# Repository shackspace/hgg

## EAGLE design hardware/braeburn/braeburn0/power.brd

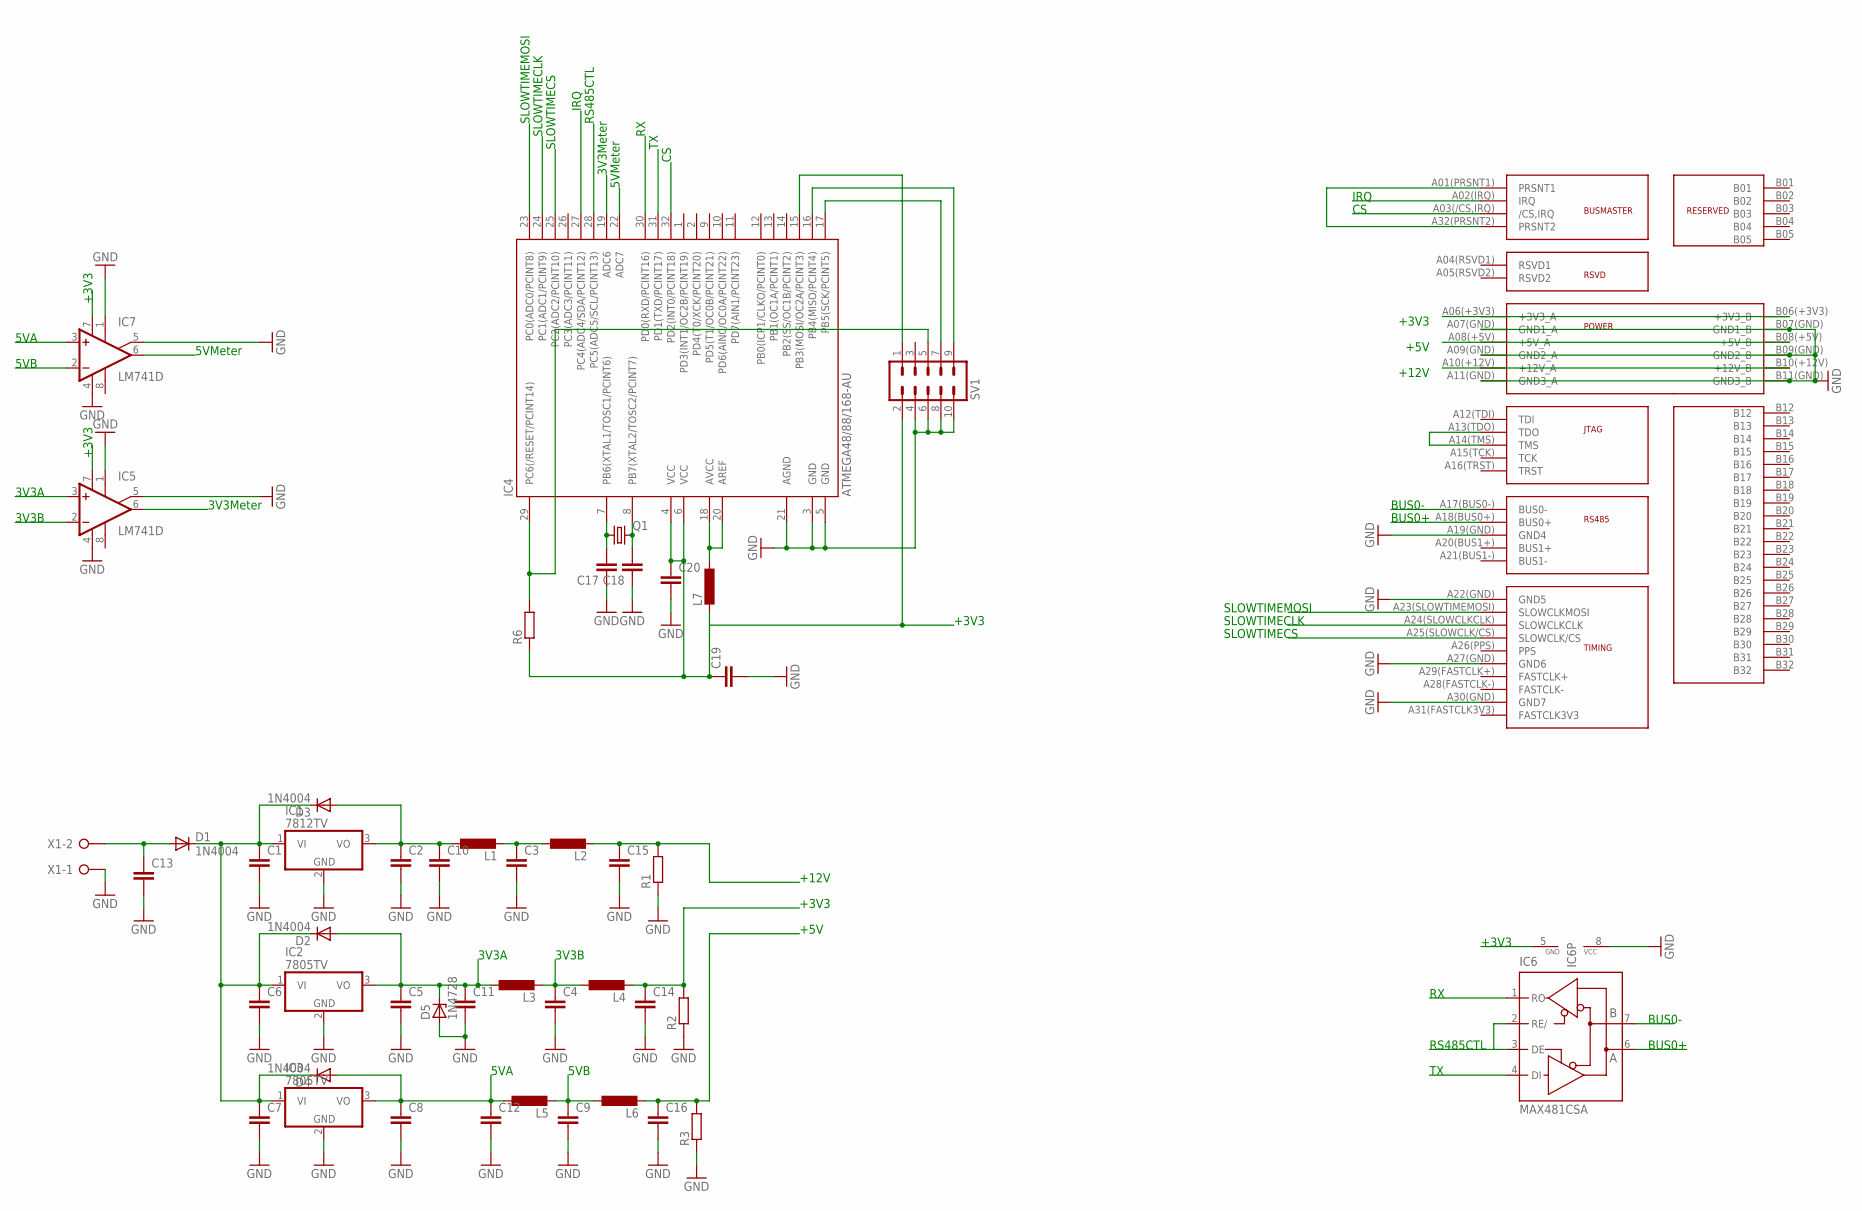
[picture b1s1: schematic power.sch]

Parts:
C1, C2, C3, C4, C5, C6, C7, C8, C9, C17, C18, C19, C20: C-EUC0805; C0805
C10, C11, C12: C-EU025-050X050; C025-050X050
C13: C-EU025-060X050; C025-060X050
C14, C15, C16: C2.5/6; C2.5-6
D1, D2, D3, D4: 1N4004; DO41-10
D5: 1N4728; DO41Z10
IC1: 7812TV; TO220V
IC2, IC3: 7805TV; TO220V
IC4: ATMEGA48/88/168-AU; TQFP32-08
IC5, IC7: LM741D; SO08
IC6: MAX481CSA; SO08
L1, L2, L3, L4, L5, L6, L7: L-EU0207/5V; 0207/5V
Q1: CRYSTALHC49U-V; HC49U-V
R1, R2, R3: R-EU_0207/15; 0207/15
R6: R-EU_R0805; R0805
SV1: MA05-2
U$1: FRIENDSHIPCONNECTOR; FRIENDSHIP_EDGE_CONNECTOR
U$2: HGG_LOGO
X1: W237-02P; W237-132

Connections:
3V3A: C5.1, C11.1, D2.A, D5.C, IC2.3 (VO), IC5.3 (+IN), L3.1
3V3B: C4.1, IC5.2 (-IN), L3.2, L4.1
3V3METER: IC4.19 (ADC6), IC5.6 (OUT)
5VA: C8.1, C12.1, D4.A, IC3.3 (VO), IC7.3 (+IN), L5.1
5VB: C9.1, IC7.2 (-IN), L5.2, L6.1
5VMETER: IC4.22 (ADC7), IC7.6 (OUT)
+3V3: C14.1, C19.1, C20.1, IC4.4 (VCC), IC4.6 (VCC), IC5.7 (V+), IC6.5 (GND), IC7.7 (V+), L4.2, L7.2, R2.2, R6.1, SV1.2, U$1.A06(+3V3) (+3V3_A), U$1.B06(+3V3) (+3V3_B)
+5V: C16.1, L6.2, R3.2, U$1.A08(+5V) (+5V_A), U$1.B08(+5V) (+5V_B)
+12V: C15.1, L2.2, R1.2, U$1.A10(+12V) (+12V_A), U$1.B10(+12V) (+12V_B)
BUS0+: IC6.6 (A), U$1.A18(BUS0+) (BUS0+)
BUS0-: IC6.7 (B), U$1.A17(BUS0-) (BUS0-)
BUSCTL: IC4.28 (PC5(ADC5/SCL/PCINT13)), IC6.2 (RE/), IC6.3 (DE)
CS: IC4.32 (PD2(INT0/PCINT18)), U$1.A03(/CS,IRQ) (/CS,IRQ)
GND: C1.2, C2.2, C3.2, C4.2, C5.2, C6.2, C7.2, C8.2, C9.2, C10.2, C11.2, C12.2, C13.2, C14.2, C15.2, C16.2, C17.1, C18.1, C19.2, C20.2, D5.A, IC1.2 (GND), IC2.2 (GND), IC3.2 (GND), IC4.3 (GND), IC4.5 (GND), IC4.21 (AGND), IC5.1 (ON1), IC5.4 (V-), IC5.5 (ON2), IC6.8 (VCC), IC7.1 (ON1), IC7.4 (V-), IC7.5 (ON2), R1.1, R2.1, R3.1, SV1.4, SV1.6, SV1.8, SV1.10, U$1.A07(GND) (GND1_A), U$1.A09(GND) (GND2_A), U$1.A11(GND) (GND3_A), U$1.A19(GND) (GND4), U$1.A22(GND) (GND5), U$1.A27(GND) (GND6), U$1.A30(GND) (GND7), U$1.B07(GND) (GND1_B), U$1.B09(GND) (GND2_B), U$1.B11(GND) (GND3_B), X1.1
IRQ: IC4.27 (PC4(ADC4/SDA/PCINT12)), U$1.A02(IRQ) (IRQ)
unnamed: C1.1, C6.1, C7.1, D1.C, D2.C, D3.C, D4.C, IC1.1 (VI), IC2.1 (VI), IC3.1 (VI)
unnamed: C18.2, IC4.8 (PB7(XTAL2/TOSC2/PCINT7)), Q1.2
unnamed: C2.1, C10.1, D3.A, IC1.3 (VO), L1.1
unnamed: C3.1, L1.2, L2.1
unnamed: C13.1, D1.A, X1.2
unnamed: C17.2, IC4.7 (PB6(XTAL1/TOSC1/PCINT6)), Q1.1
unnamed: IC4.29 (PC6(/RESET/PCINT14)), R6.2, SV1.5
unnamed: IC4.18 (AVCC), IC4.20 (AREF), L7.1
unnamed: IC4.16 (PB4(MISO/PCINT4)), SV1.9
unnamed: IC4.17 (PB5(SCK/PCINT5)), SV1.7
unnamed: IC4.15 (PB3(MOSI/OC2A/PCINT3)), SV1.1
unnamed: U$1.A13(TDO) (TDO), U$1.A14(TMS) (TMS)
unnamed: U$1.A01(PRSNT1) (PRSNT1), U$1.A32(PRSNT2) (PRSNT2)
RX: IC4.30 (PD0(RXD/PCINT16)), IC6.1 (RO)
SLOWTIMECLK: IC4.24 (PC1(ADC1/PCINT9)), U$1.A24(SLOWCLKCLK) (SLOWCLKCLK)
SLOWTIMECS: IC4.25 (PC2(ADC2/PCINT10)), U$1.A25(SLOWCLK/CS) (SLOWCLK/CS)
SLOWTIMEMOSI: IC4.23 (PC0(ADC0/PCINT8)), U$1.A23(SLOWTIMEMOSI) (SLOWCLKMOSI)
TX: IC4.31 (PD1(TXD/PCINT17)), IC6.4 (DI)

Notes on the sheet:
BUS0-
BUS0+
RS485CTL
IRQ
+5V
+3V3
+12V
SLOWTIMEMOSI
SLOWTIMECLK
SLOWTIMECS
3V3Meter
5VMeter
3V3A
3V3B
5VA
5VB

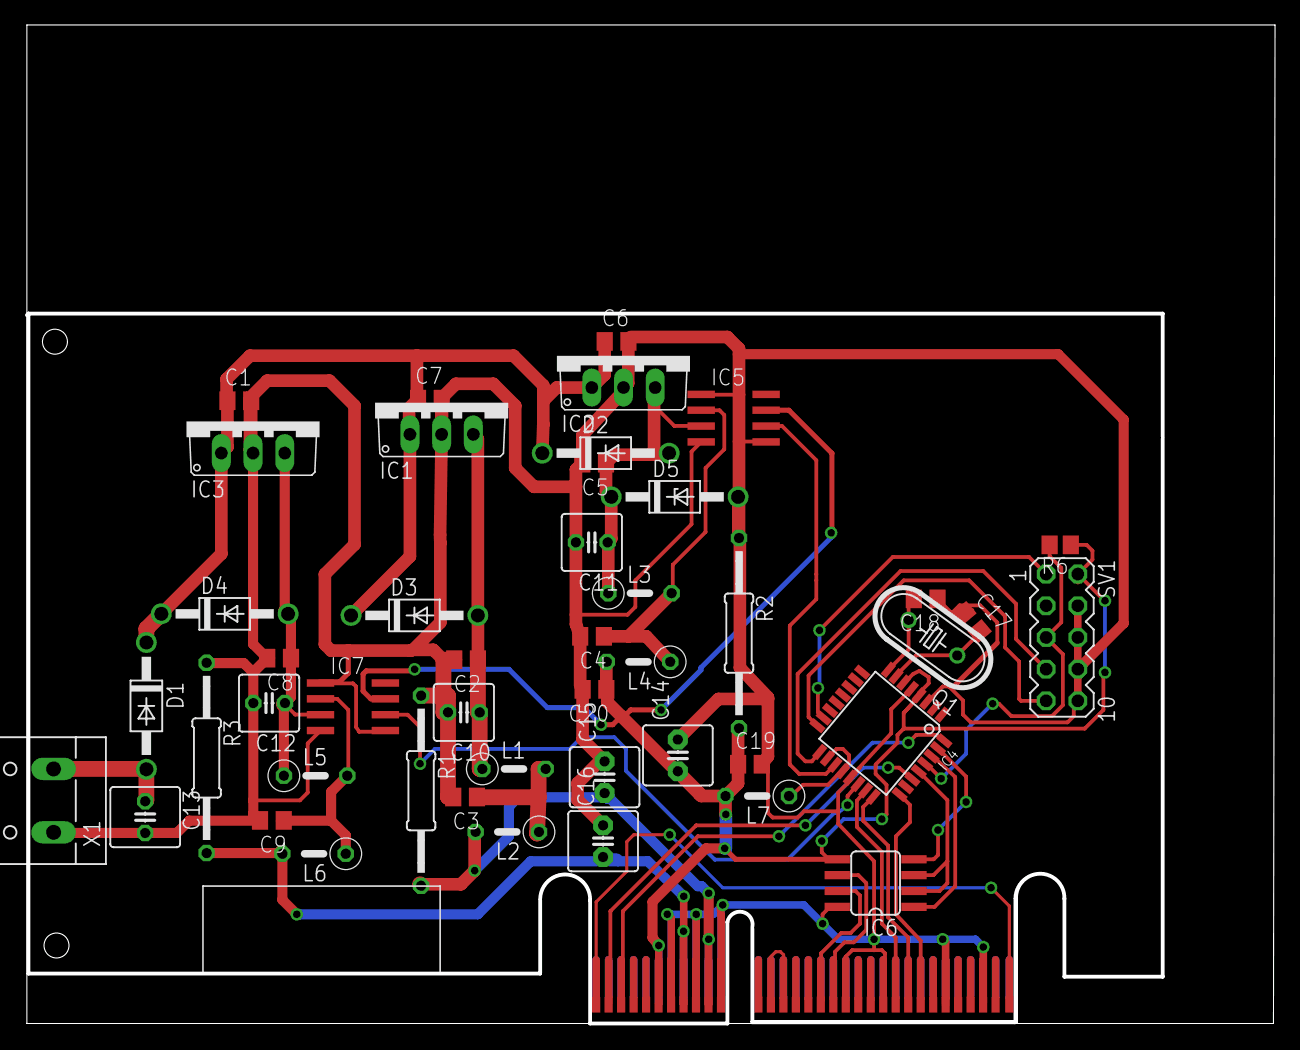
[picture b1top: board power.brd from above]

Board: 2 copper layers, 100.0 x 80.0 mm, 48 parts (0 on the bottom side), 33 nets.

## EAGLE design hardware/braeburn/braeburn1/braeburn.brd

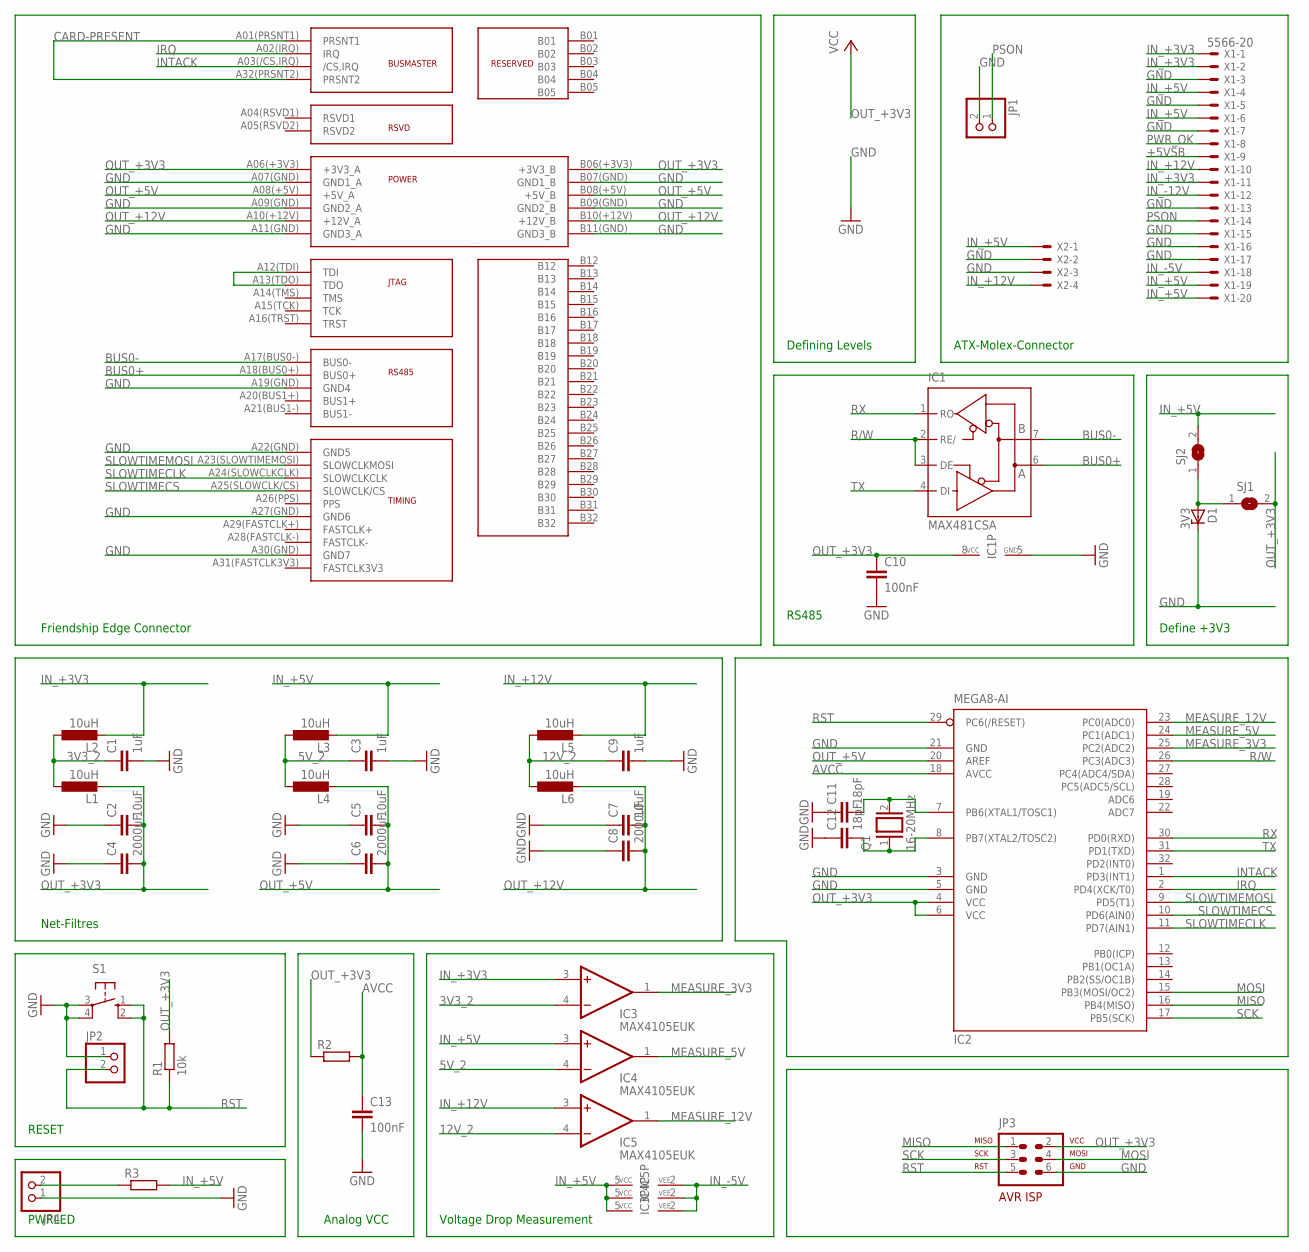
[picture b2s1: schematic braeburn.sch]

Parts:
C1, C3, C9: 1uF; C0805
C2, C5, C7: 10uF; C0603
C4, C6, C8: 2000uF; C025-060X050
C10, C13: 100nF; C0603
C11, C12: 18pF; C0603
D1: 3V3; DO41Z10
IC1: MAX481CSA; SO08
IC2: MEGA8-AI; TQFP32-08
IC3, IC4, IC5: MAX4105EUK; SOT23-5L
JP1, JP2, JP4: PINHD-1X2; 1X02
JP3: AVR-ISP-6VERT; AVR-ISP-6
L1, L2, L3, L4, L5, L6: 10uH; 0207/5V
Q1: 16-20MHz; QS
R1: 10k; R0603
R2, R3: R-EU_R0603; R0603
S1: 10-XX; B3F-10XX
SJ1, SJ2: SJW
U$1: FRIENDSHIPCONNECTOR; FRIENDSHIP_EDGE_CONNECTOR
X1: 5566-20
X2: KK-156-4

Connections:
3V3_2: C1.1, IC3.4 (-IN), L1.1, L2.1
5V_2: C3.1, IC4.4 (-IN), L3.1, L4.1
12V_2: C9.1, IC5.4 (-IN), L5.1, L6.1
+5VSB: X1.9
AVCC: C13.1, IC2.18 (AVCC), R2.2
BUS0+: IC1.6 (A), U$1.A18(BUS0+) (BUS0+)
BUS0-: IC1.7 (B), U$1.A17(BUS0-) (BUS0-)
CARD-PRESENT: U$1.A01(PRSNT1) (PRSNT1), U$1.A32(PRSNT2) (PRSNT2)
GND: C1.2, C2.1, C3.2, C4.1, C5.1, C6.1, C7.1, C8.1, C9.2, C10.2, C11.1, C12.1, C13.2, D1.C, IC1.5 (GND), IC2.3 (GND), IC2.5 (GND), IC2.21 (GND), JP1.2, JP2.1, JP3.6, JP4.1, S1.3, S1.4 (P1), U$1.A07(GND) (GND1_A), U$1.A09(GND) (GND2_A), U$1.A11(GND) (GND3_A), U$1.A19(GND) (GND4), U$1.A22(GND) (GND5), U$1.A27(GND) (GND6), U$1.A30(GND) (GND7), U$1.B07(GND) (GND1_B), U$1.B09(GND) (GND2_B), U$1.B11(GND) (GND3_B), X1.3, X1.5, X1.7, X1.13, X1.15, X1.16, X1.17, X2.2, X2.3
INTACK: IC2.1 (PD3(INT1)), U$1.A03(/CS,IRQ) (/CS,IRQ)
IN_+3V3: IC3.3 (+IN), L2.2, X1.1, X1.2, X1.11
IN_+5V: IC3.5 (VCC), IC4.3 (+IN), IC4.5 (VCC), IC5.5 (VCC), L3.2, R3.2, SJ2.2, X1.4, X1.6, X1.19, X1.20, X2.1
IN_+12V: IC5.3 (+IN), L5.2, X1.10, X2.4
IN_-5V: IC3.2 (VEE), IC4.2 (VEE), IC5.2 (VEE), X1.18
IN_-12V: X1.12
IRQ: IC2.2 (PD4(XCK/T0)), U$1.A02(IRQ) (IRQ)
MEASURE_3V3: IC2.25 (PC2(ADC2)), IC3.1 (OUT)
MEASURE_5V: IC2.24 (PC1(ADC1)), IC4.1 (OUT)
MEASURE_12V: IC2.23 (PC0(ADC0)), IC5.1 (OUT)
MISO: IC2.16 (PB4(MISO)), JP3.1
MOSI: IC2.15 (PB3(MOSI/OC2)), JP3.4
unnamed: U$1.A12(TDI) (TDI), U$1.A13(TDO) (TDO)
unnamed: JP4.2, R3.1
unnamed: C11.2, IC2.7 (PB6(XTAL1/TOSC1)), Q1.2
unnamed: C12.2, IC2.8 (PB7(XTAL2/TOSC2)), Q1.1
unnamed: D1.A, SJ1.1, SJ2.1
OUT_+3V3: C2.2, C4.2, C10.1, IC1.8 (VCC), IC2.4 (VCC), IC2.6 (VCC), JP3.2, L1.2, R1.2, R2.1, SJ1.2, U$1.A06(+3V3) (+3V3_A), U$1.B06(+3V3) (+3V3_B)
OUT_+5V: C5.2, C6.2, IC2.20 (AREF), L4.2, U$1.A08(+5V) (+5V_A), U$1.B08(+5V) (+5V_B)
OUT_+12V: C7.2, C8.2, L6.2, U$1.A10(+12V) (+12V_A), U$1.B10(+12V) (+12V_B)
PSON: JP1.1, X1.14
PWR_OK: X1.8
R/W: IC1.2 (RE/), IC1.3 (DE), IC2.26 (PC3(ADC3))
RST: IC2.29 (PC6(/RESET)), JP2.2, JP3.5, R1.1, S1.1 (S), S1.2 (S1)
RX: IC1.1 (RO), IC2.30 (PD0(RXD))
SCK: IC2.17 (PB5(SCK)), JP3.3
SLOWTIMECLK: IC2.11 (PD7(AIN1)), U$1.A24(SLOWCLKCLK) (SLOWCLKCLK)
SLOWTIMECS: IC2.10 (PD6(AIN0)), U$1.A25(SLOWCLK/CS) (SLOWCLK/CS)
SLOWTIMEMOSI: IC2.9 (PD5(T1)), U$1.A23(SLOWTIMEMOSI) (SLOWCLKMOSI)
TX: IC1.4 (DI), IC2.31 (PD1(TXD))

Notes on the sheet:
ATX-Molex-Connector
Friendship Edge Connector
RS485
Net-Filtres
RESET
Analog VCC
Voltage Drop Measurement
Defining Levels
Define +3V3
PWRLED

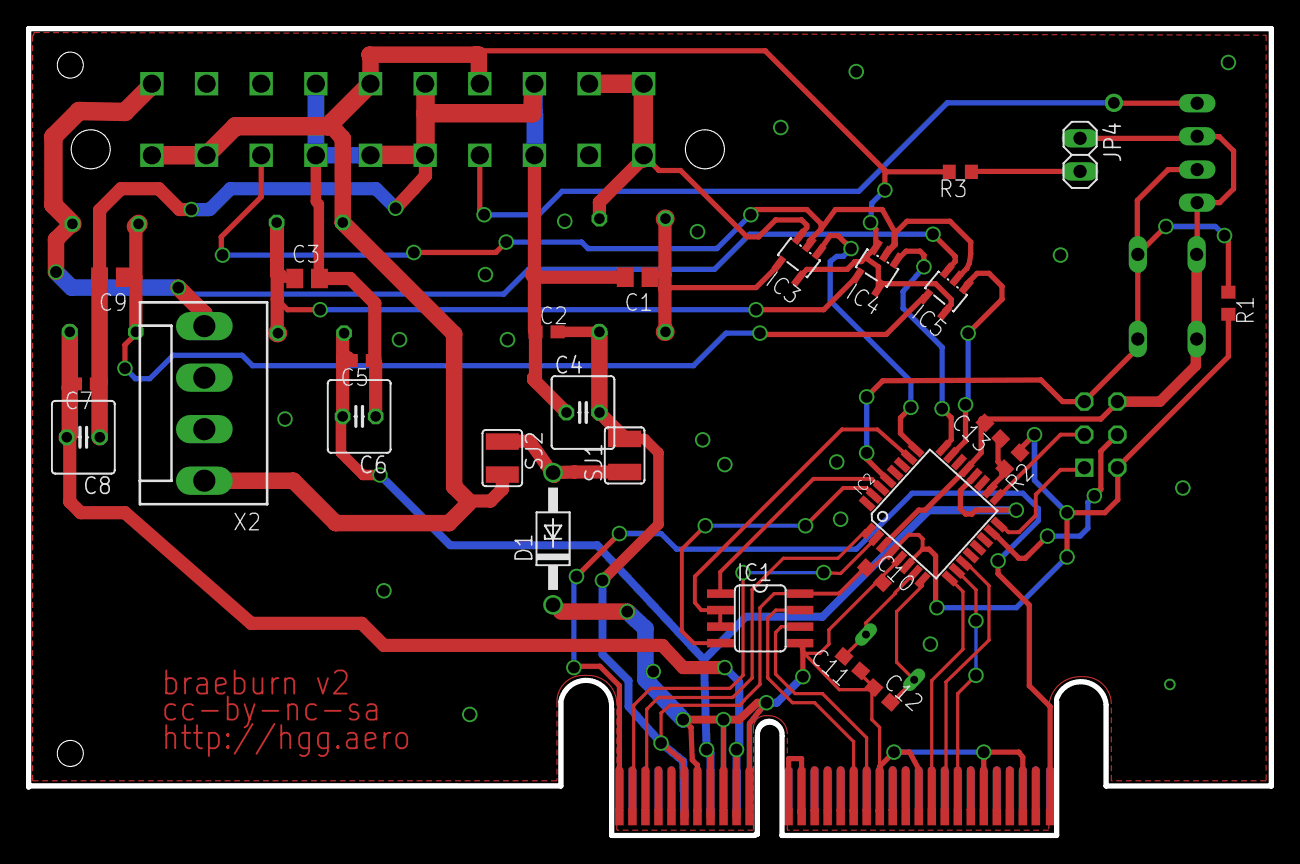
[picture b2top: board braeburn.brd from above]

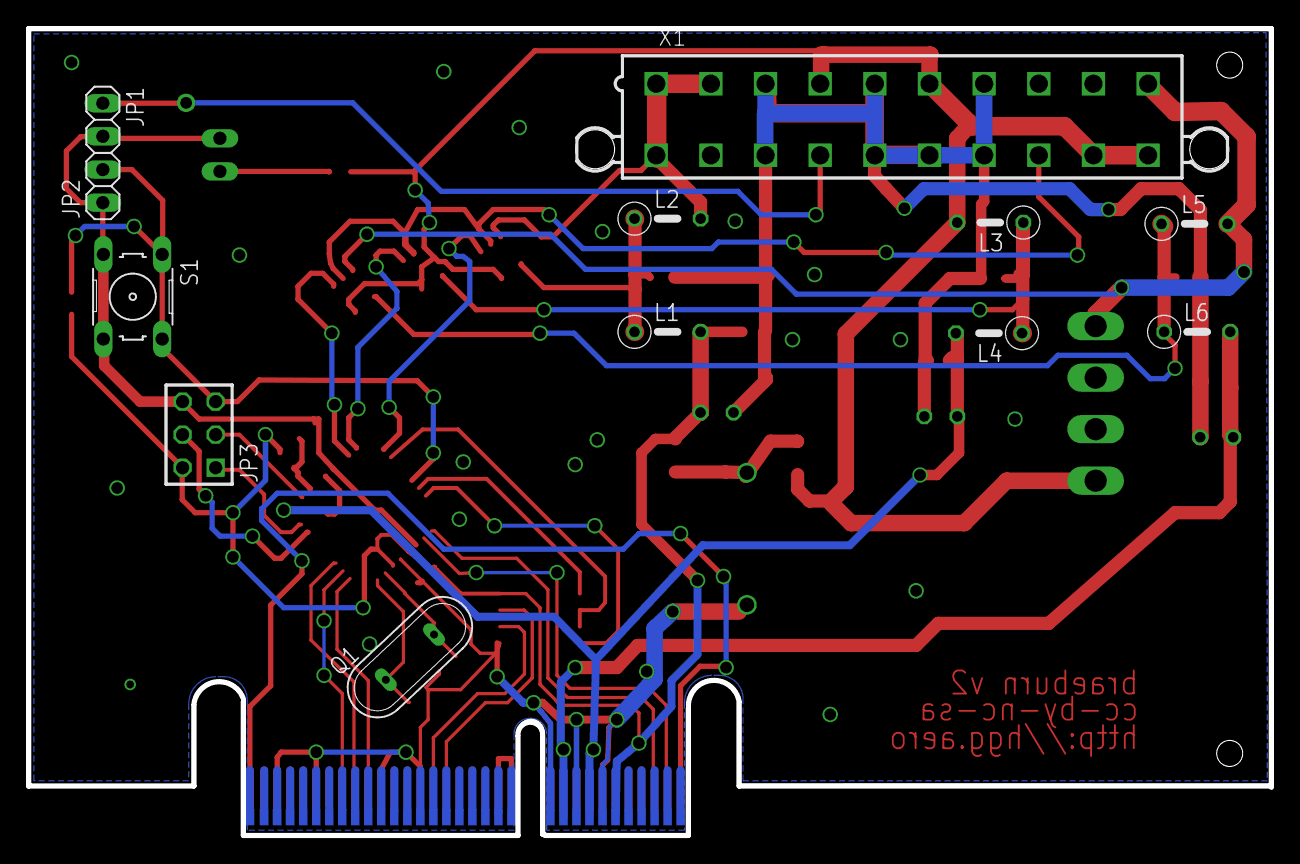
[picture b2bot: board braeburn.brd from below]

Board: 4 copper layers, 95.5 x 62.0 mm, 39 parts (12 on the bottom side), 36 nets.

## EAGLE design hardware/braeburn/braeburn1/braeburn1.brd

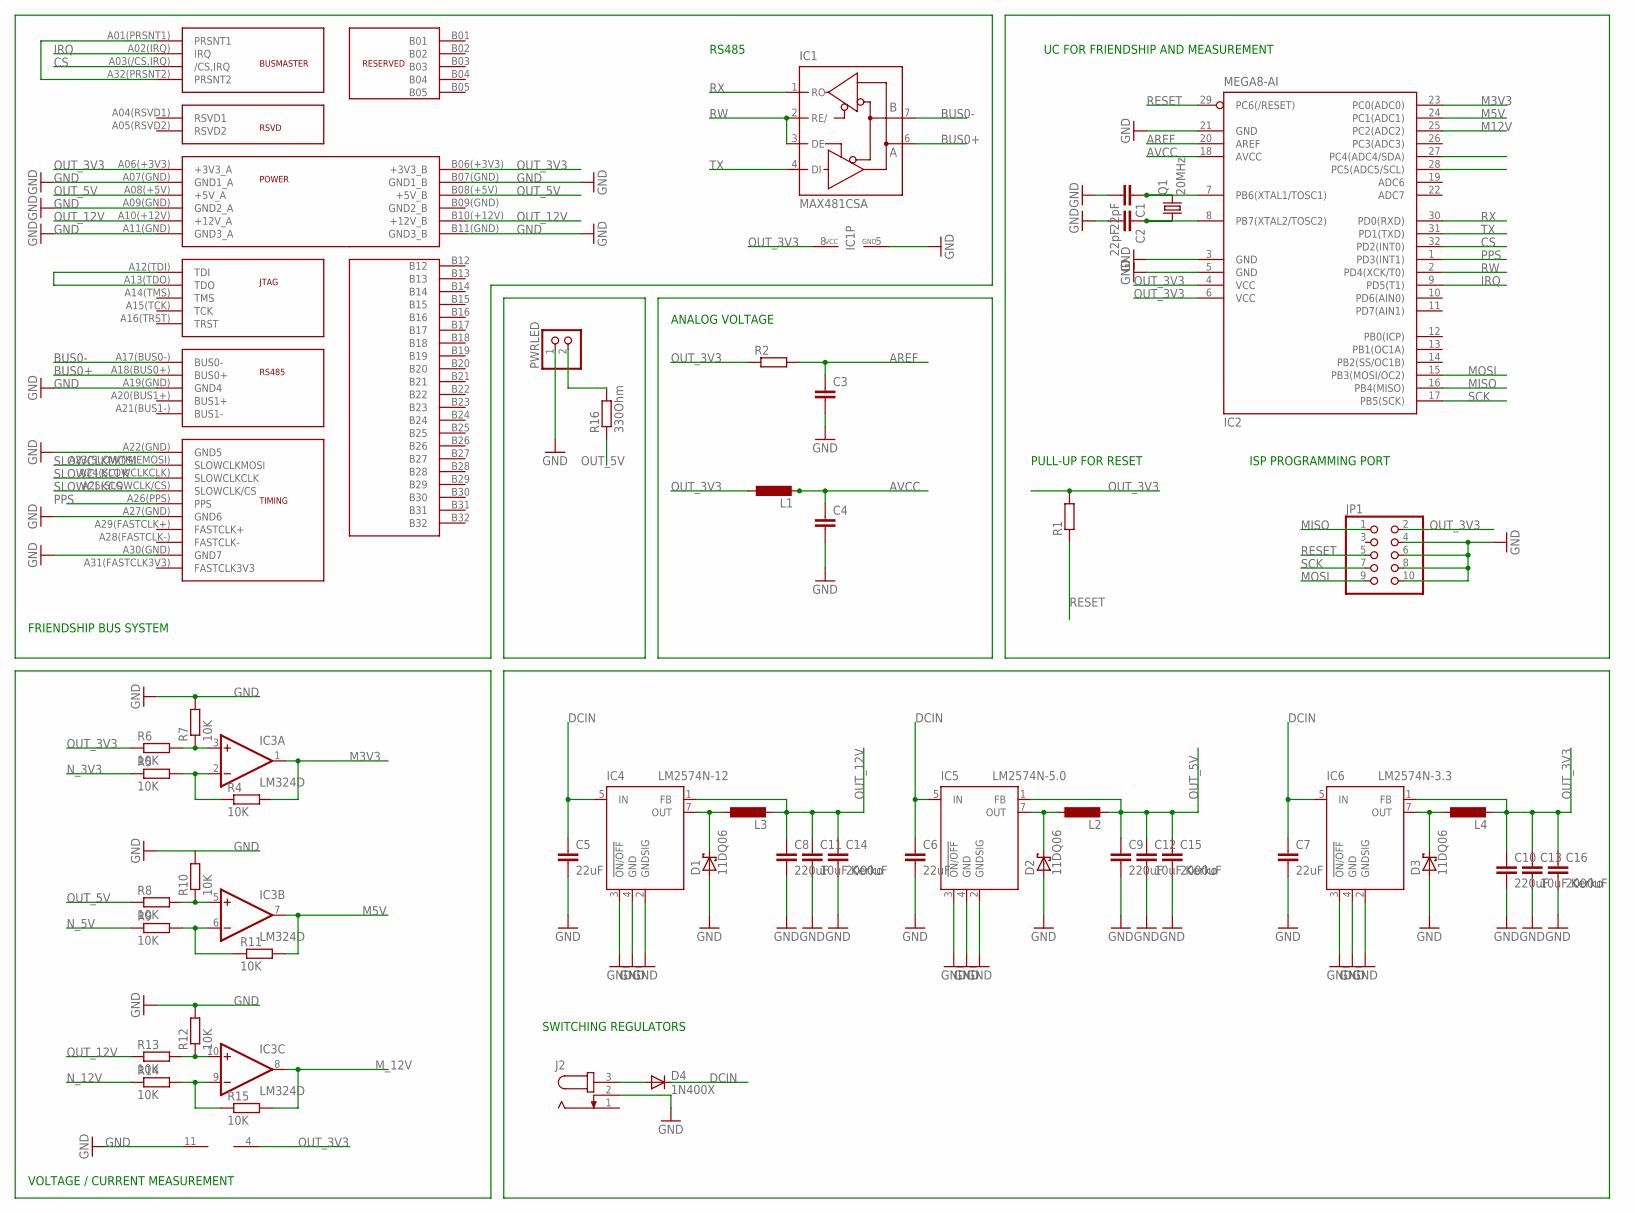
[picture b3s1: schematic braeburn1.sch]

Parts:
C1, C2: 22pF; C0603
C3, C4: C-EUC0603; C0603
C5, C6, C7: 22uF; C025-050X050
C8, C9, C10: 220uF; C025-050X050
C11, C12, C13: 10uF Kerko; C0603
C14, C15, C16: 2000uF; C050-075X075
D1, D2, D3: 11DQ06; DO41-7.6
D4: 1N400X; DO41-10
IC1: MAX481CSA; SO08
IC2: MEGA8-AI; TQFP32-08
IC3: LM324D; SO14
IC4: LM2574N-12; DIL08
IC5: LM2574N-5.0; DIL08
IC6: LM2574N-3.3; DIL08
J2: JACK-PLUG0; SPC4077
JP1: PINHD-2X5; 2X05
L1: L-EU0207/5V; 0207/5V
L2, L3, L4: L-EUPIS2816; PIS2816
PWRLED: PINHD-1X2; 1X02
Q1: 20MHz; HC33U-V
R1, R2: R-EU_R0603; R0603
R4, R5, R6, R7, R8, R9, R10, R11, R12, R13, R14, R15: 10K; R0603
R16: 330Ohm; R0603
U$1: FRIENDSHIPCONNECTOR; FRIENDSHIP_EDGE_CONNECTOR

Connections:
AREF: C3.1, IC2.20 (AREF), R2.2
AVCC: C4.1, IC2.18 (AVCC), L1.2
BUS0+: IC1.6 (A), U$1.A18(BUS0+) (BUS0+)
BUS0-: IC1.7 (B), U$1.A17(BUS0-) (BUS0-)
CS: IC2.32 (PD2(INT0)), U$1.A03(/CS,IRQ) (/CS,IRQ)
DCIN: C5.1, C6.1, C7.1, D4.C, IC4.5 (IN), IC5.5 (IN), IC6.5 (IN)
GND: C1.2, C2.2, C3.2, C4.2, C5.2, C6.2, C7.2, C8.2, C9.2, C10.2, C11.2, C12.2, C13.2, C14.2, C15.2, C16.2, D1.A, D2.A, D3.A, IC1.5 (GND), IC2.3 (GND), IC2.5 (GND), IC2.21 (GND), IC3.11 (V-), IC4.2 (GNDSIG), IC4.3 (!ON/OFF), IC4.4 (GND), IC5.2 (GNDSIG), IC5.3 (!ON/OFF), IC5.4 (GND), IC6.2 (GNDSIG), IC6.3 (!ON/OFF), IC6.4 (GND), J2.2, JP1.4, JP1.6, JP1.8, JP1.10, PWRLED.1, R7.2, R10.2, R12.2, U$1.A07(GND) (GND1_A), U$1.A09(GND) (GND2_A), U$1.A11(GND) (GND3_A), U$1.A19(GND) (GND4), U$1.A22(GND) (GND5), U$1.A30(GND) (GND7), U$1.B07(GND) (GND1_B), U$1.B11(GND) (GND3_B)
IRQ: IC2.9 (PD5(T1)), U$1.A02(IRQ) (IRQ)
M3V3: IC2.23 (PC0(ADC0)), IC3.1 (OUT), R4.2
M5V: IC2.24 (PC1(ADC1)), IC3.7 (OUT), R11.2
M12V: IC2.25 (PC2(ADC2))
MISO: IC2.16 (PB4(MISO)), JP1.1
MOSI: IC2.15 (PB3(MOSI/OC2)), JP1.9
M_12V: IC3.8 (OUT), R15.2
unnamed: U$1.A01(PRSNT1) (PRSNT1), U$1.A32(PRSNT2) (PRSNT2)
unnamed: U$1.A12(TDI) (TDI), U$1.A13(TDO) (TDO)
unnamed: C1.1, IC2.7 (PB6(XTAL1/TOSC1)), Q1.2
unnamed: C2.1, IC2.8 (PB7(XTAL2/TOSC2)), Q1.1
unnamed: IC3.2 (-IN), R4.1, R5.2
unnamed: IC3.3 (+IN), R6.2, R7.1
unnamed: IC3.6 (-IN), R9.2, R11.1
unnamed: D4.A, J2.3
unnamed: IC3.5 (+IN), R8.2, R10.1
unnamed: PWRLED.2, R16.2
unnamed: IC3.10 (+IN), R12.1, R13.2
unnamed: IC3.9 (-IN), R14.2, R15.1
N_3V3: D3.C, IC6.7 (OUT), L4.1, R5.1
N_5V: D2.C, IC5.7 (OUT), L2.1, R9.1
N_12V: D1.C, IC4.7 (OUT), L3.1, R14.1
OUT_3V3: C10.1, C13.1, C16.1, IC1.8 (VCC), IC2.4 (VCC), IC2.6 (VCC), IC3.4 (V+), IC6.1 (FB), JP1.2, L1.1, L4.2, R1.2, R2.1, R6.1, U$1.A06(+3V3) (+3V3_A), U$1.B06(+3V3) (+3V3_B)
OUT_5V: C9.1, C12.1, C15.1, IC5.1 (FB), L2.2, R8.1, R16.1, U$1.A08(+5V) (+5V_A), U$1.B08(+5V) (+5V_B)
OUT_12V: C8.1, C11.1, C14.1, IC4.1 (FB), L3.2, R13.1, U$1.A10(+12V) (+12V_A), U$1.B10(+12V) (+12V_B)
PPS: IC2.1 (PD3(INT1)), U$1.A26(PPS) (PPS)
RESET: IC2.29 (PC6(/RESET)), JP1.5, R1.1
RW: IC1.2 (RE/), IC1.3 (DE), IC2.2 (PD4(XCK/T0))
RX: IC1.1 (RO), IC2.30 (PD0(RXD))
SCK: IC2.17 (PB5(SCK)), JP1.7
SLOWCLKCLK: U$1.A24(SLOWCLKCLK) (SLOWCLKCLK)
SLOWCLKCS: U$1.A25(SLOWCLK/CS) (SLOWCLK/CS)
SLOWCLKMOSI: U$1.A23(SLOWTIMEMOSI) (SLOWCLKMOSI)
TX: IC1.4 (DI), IC2.31 (PD1(TXD))

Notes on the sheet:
FRIENDSHIP BUS SYSTEM
RS485
PULL-UP FOR RESET
ISP PROGRAMMING PORT
UC FOR FRIENDSHIP AND MEASUREMENT
ANALOG VOLTAGE
VOLTAGE / CURRENT MEASUREMENT
SWITCHING REGULATORS

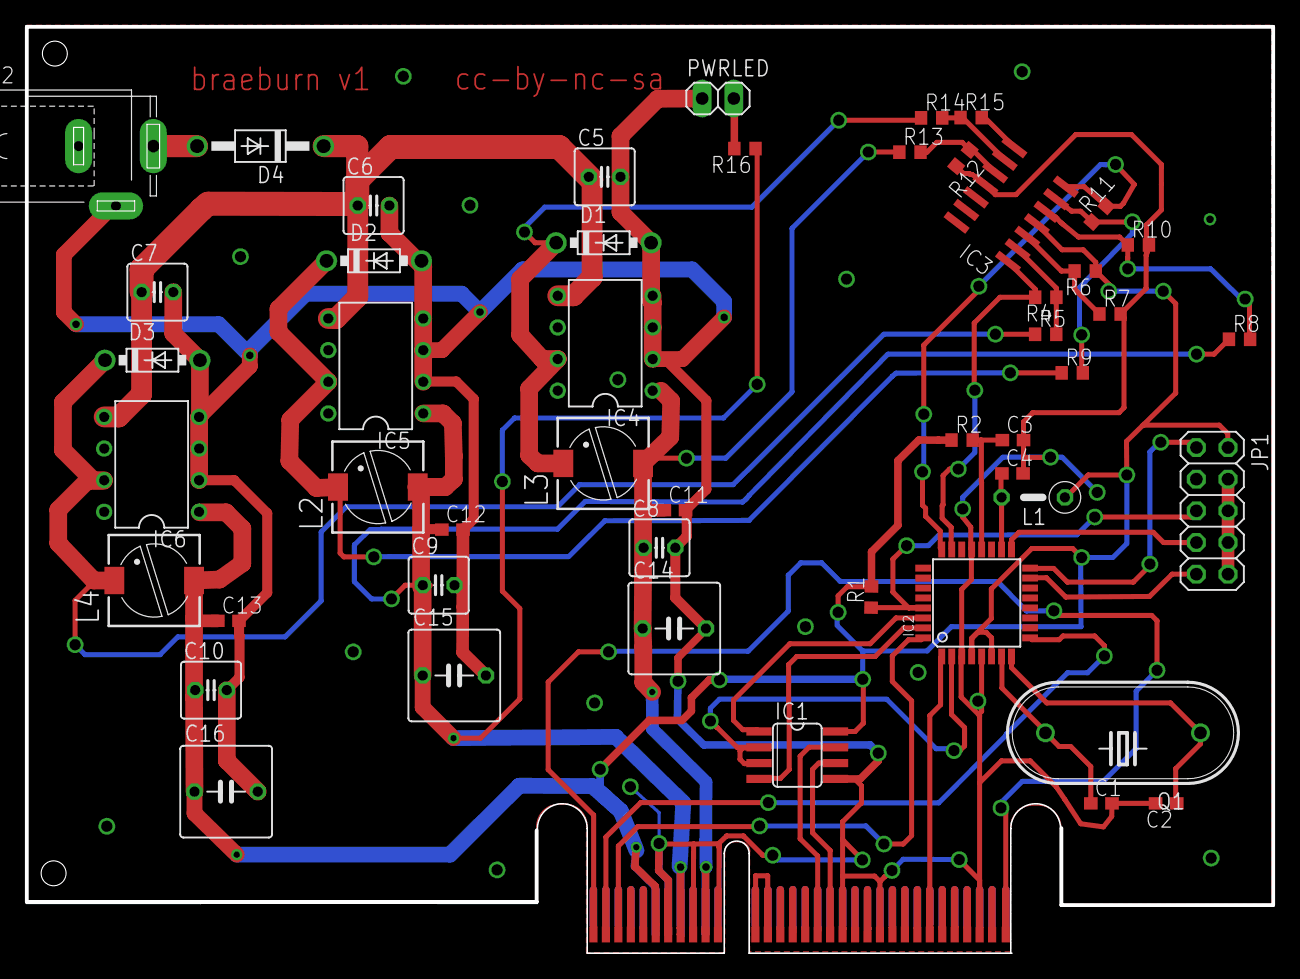
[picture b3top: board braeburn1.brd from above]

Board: 2 copper layers, 100.1 x 74.4 mm, 50 parts (0 on the bottom side), 37 nets.

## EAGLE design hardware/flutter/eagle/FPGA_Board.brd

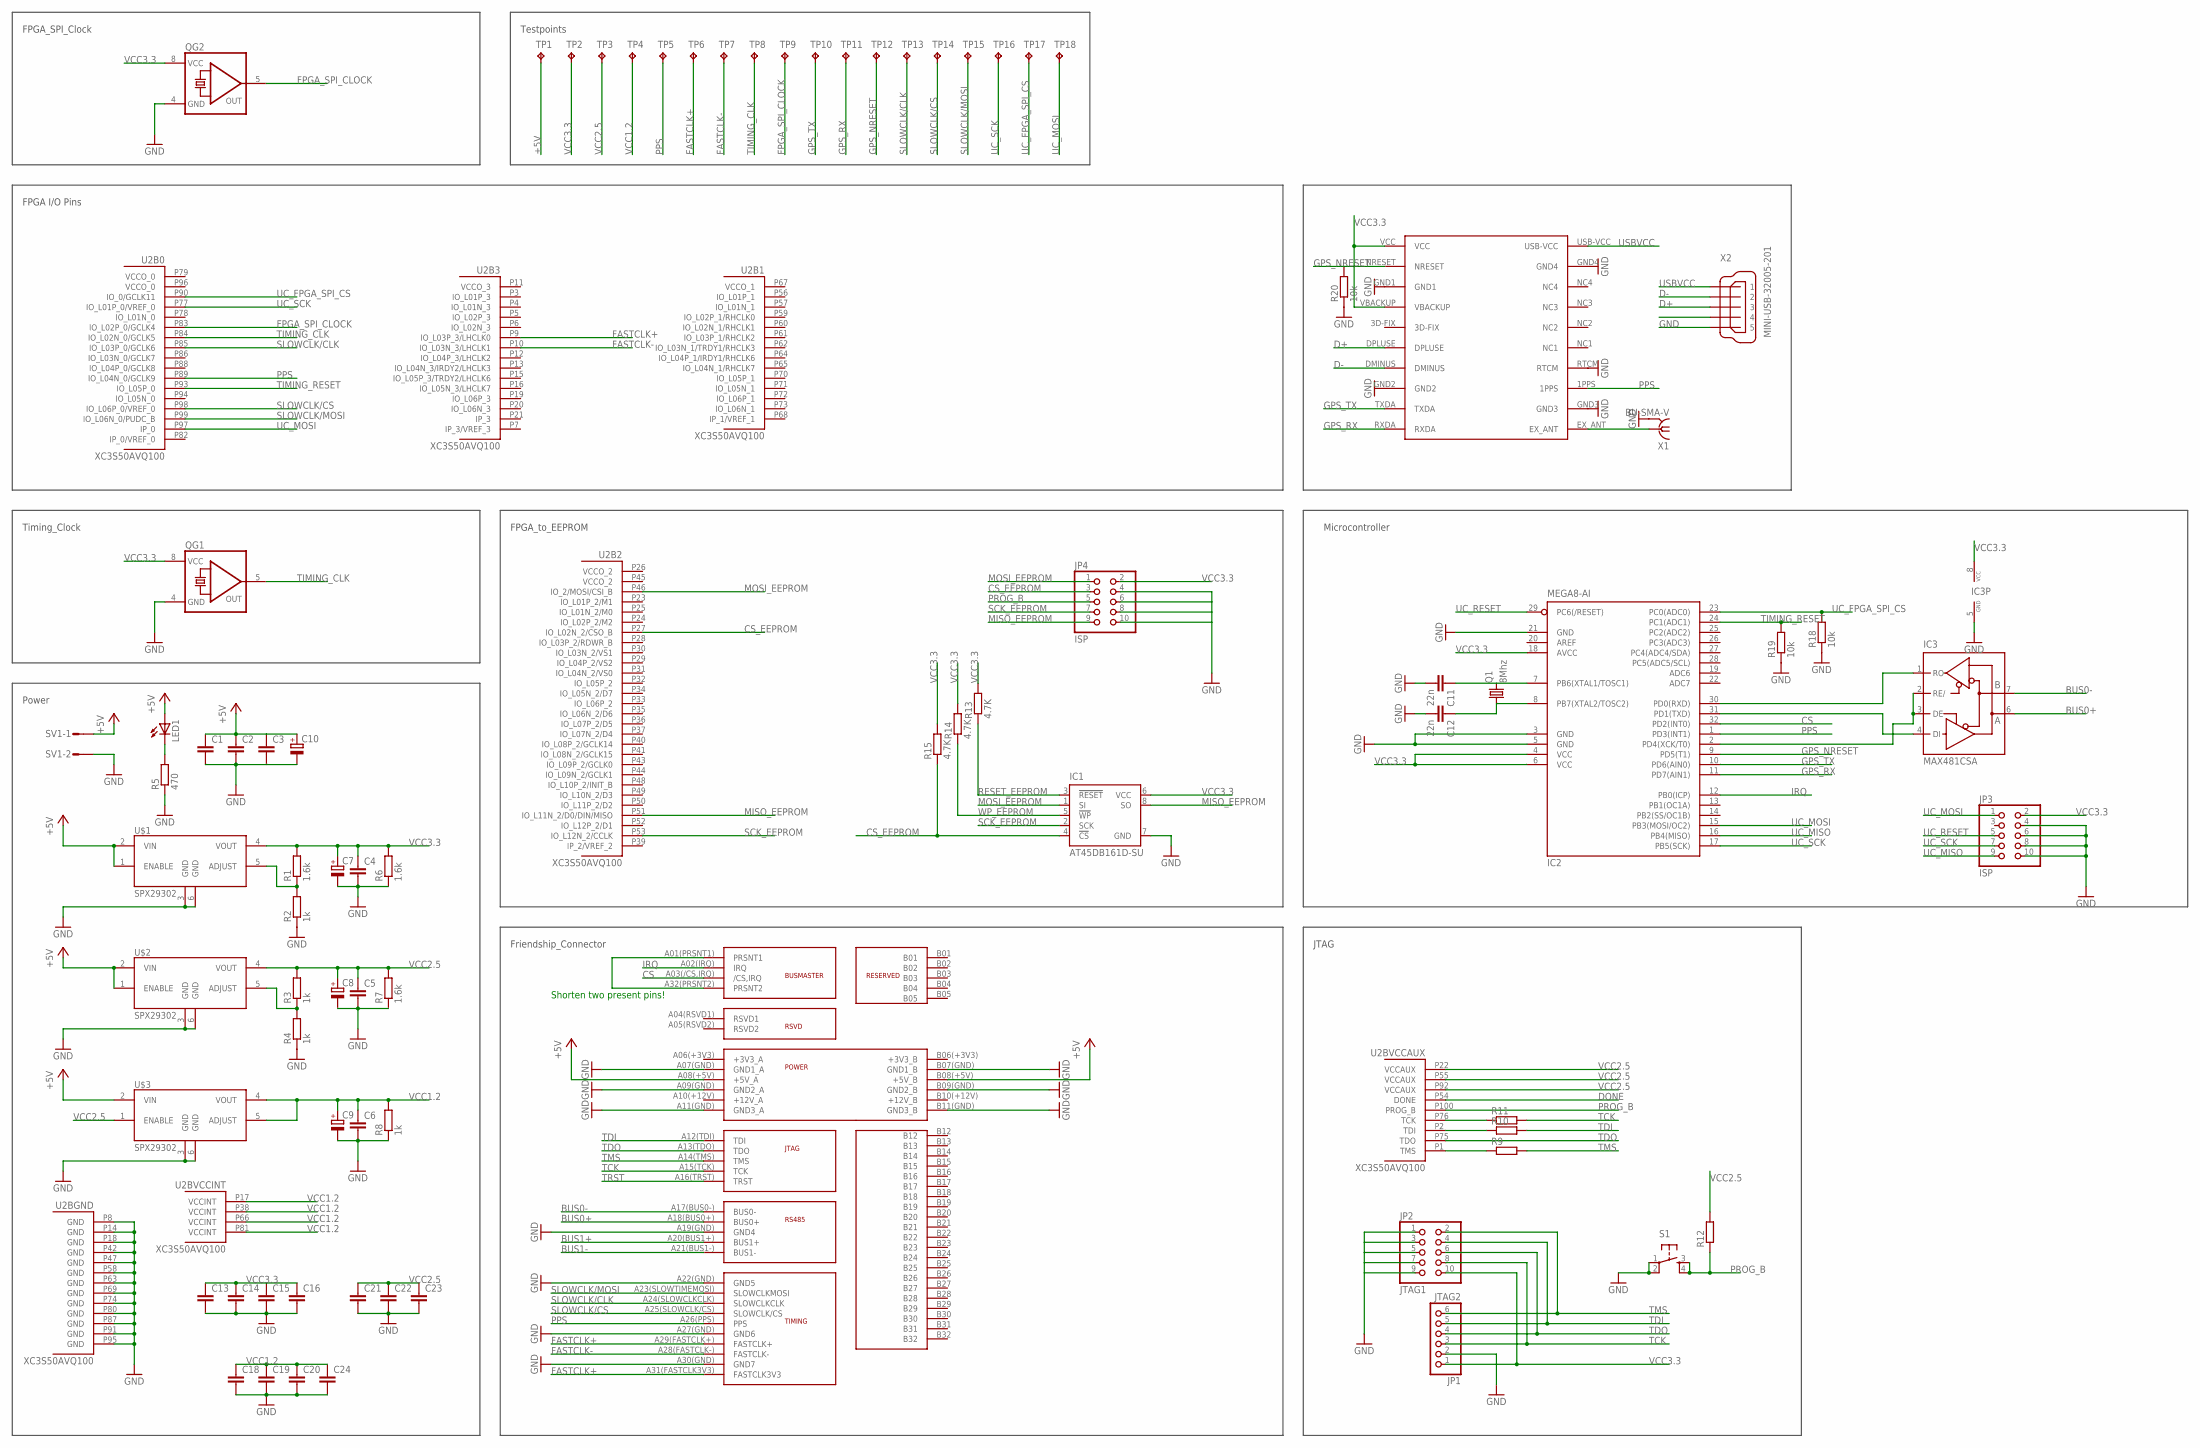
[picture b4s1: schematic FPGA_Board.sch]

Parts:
C1, C2, C3, C4, C5, C6: C-EUC0805; C0805
C7, C8, C9, C10: CPOL-EU085CS-1AR; 085CS_1AR
C11, C12: 22n; C0805
C13, C14, C15, C16, C18, C19, C20, C21, C22, C23, C24: C-EUC0603; C0603
IC1: AT45DB161D-SU; 8S2
IC2: MEGA8-AI; TQFP32-08
IC3: MAX481CSA; SO08
JP1: JTAG2; 1X06
JP2: JTAG1; 2X05
JP3, JP4: ISP; 2X05
LED1: LEDCHIPLED_0805; CHIPLED_0805
Q1: 8Mhz; HC49UP
QG1, QG2: QG5460; DIL08S
R1, R6, R7: 1.6k; M0805
R2, R3, R4, R8: 1k; M0805
R5: 470; M0805
R9, R10, R11, R12: R-EU_M0805; M0805
R13, R14, R15: 4.7K; M0805
R18, R19, R20: 10k; M0805
S1: TAC_SWITCHPTH; TACTILE-PTH
SV1: L02P
TP1, TP2, TP3, TP4, TP5, TP6, TP7, TP8, TP9, TP10, TP11, TP12, TP13, TP14, TP15, TP16, TP17, TP18: TPB2,54; B2,54
U2: XC3S50AVQ100; VQ100
U$1, U$2, U$3: SPX29302; Q5-DD_SPX29300
U$4: FRIENDSHIPCONNECTOR; FRIENDSHIP_EDGE_CONNECTOR
U$5: HGG_LOGO
U$6: GPS
X1: BU-SMA-V
X2: MINI-USB-32005-201; 32005-201

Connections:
+5V: C1.1, C2.1, C3.1, C10.+, LED1.A, SV1.1, TP1.TP, U$1.1 (ENABLE), U$1.2 (VIN), U$2.1 (ENABLE), U$2.2 (VIN), U$3.2 (VIN), U$4.A08(+5V) (+5V_A), U$4.B08(+5V) (+5V_B)
BUS0+: IC3.6 (A), U$4.A18(BUS0+) (BUS0+)
BUS0-: IC3.7 (B), U$4.A17(BUS0-) (BUS0-)
BUS1+: U$4.A20(BUS1+) (BUS1+)
BUS1-: U$4.A21(BUS1-) (BUS1-)
CS: IC2.32 (PD2(INT0)), U$4.A03(/CS,IRQ) (/CS,IRQ)
CS_EEPROM: IC1.4 (!CS), JP4.3, R15.1, U2.P27 (IO_L02N_2/CSO_B)
D+: U$6.DPLUSE, X2.3
D-: U$6.DMINUS, X2.2
DI: IC2.31 (PD1(TXD)), IC3.4 (DI)
DO: IC2.30 (PD0(RXD)), IC3.1 (RO)
DONE: U2.P54 (DONE)
FASTCLK+: TP6.TP, U2.P9 (IO_L03P_3/LHCLK0), U$4.A29(FASTCLK+) (FASTCLK+), U$4.A31(FASTCLK3V3) (FASTCLK3V3)
FASTCLK-: TP7.TP, U2.P10 (IO_L03N_3/LHCLK1), U$4.A28(FASTCLK-) (FASTCLK-)
FPGA_SPI_CLOCK: QG2.5 (OUT), TP9.TP, U2.P83 (IO_L02P_0/GCLK4)
GND: C1.2, C2.2, C3.2, C4.2, C5.2, C6.2, C7.-, C8.-, C9.-, C10.-, C11.2, C12.2, C13.2, C14.2, C15.2, C16.2, C18.2, C19.2, C20.2, C21.2, C22.2, C23.2, C24.2, IC1.7 (GND), IC2.3 (GND), IC2.5 (GND), IC2.21 (GND), IC3.5 (GND), JP1.2, JP2.1, JP2.3, JP2.5, JP2.7, JP2.9, JP3.4, JP3.6, JP3.8, JP3.10, JP4.4, JP4.6, JP4.8, JP4.10, QG1.4 (GND), QG2.4 (GND), R2.1, R4.1, R5.1, R6.1, R7.1, R8.1, R18.1, R19.1, R20.1, S1.1, S1.2, SV1.2, U2.P8 (GND), U2.P14 (GND), U2.P18 (GND), U2.P42 (GND), U2.P47 (GND), U2.P58 (GND), U2.P63 (GND), U2.P69 (GND), U2.P74 (GND), U2.P80 (GND), U2.P87 (GND), U2.P91 (GND), U2.P95 (GND), U$1.3 (GND), U$1.6 (GND), U$2.3 (GND), U$2.6 (GND), U$3.3 (GND), U$3.6 (GND), U$4.A07(GND) (GND1_A), U$4.A09(GND) (GND2_A), U$4.A11(GND) (GND3_A), U$4.A19(GND) (GND4), U$4.A22(GND) (GND5), U$4.A27(GND) (GND6), U$4.A30(GND) (GND7), U$4.B07(GND) (GND1_B), U$4.B09(GND) (GND2_B), U$4.B11(GND) (GND3_B), U$6.GND1, U$6.GND2, U$6.GND3, U$6.GND4, U$6.RTCM, X1.2 (GND), X1.3 (GND), X1.4 (GND), X1.5 (GND), X2.5
GPS_NRESET: IC2.9 (PD5(T1)), R20.2, TP12.TP, U$6.NRESET
GPS_RX: IC2.11 (PD7(AIN1)), TP11.TP, U$6.RXDA
GPS_TX: IC2.10 (PD6(AIN0)), TP10.TP, U$6.TXDA
IRQ: IC2.12 (PB0(ICP)), U$4.A02(IRQ) (IRQ)
MISO_EEPROM: IC1.8 (SO), JP4.9, U2.P51 (IO_L11N_2/D0/DIN/MISO)
MOSI_EEPROM: IC1.1 (SI), JP4.1, U2.P46 (IO_2/MOSI/CSI_B)
unnamed: R11.1, U2.P76 (TCK)
unnamed: R10.1, U2.P2 (TDI)
unnamed: LED1.C, R5.2
unnamed: R9.1, U2.P1 (TMS)
unnamed: IC2.2 (PD4(XCK/T0)), IC3.2 (RE/), IC3.3 (DE)
unnamed: R1.1, R2.2, U$1.5 (ADJUST)
unnamed: R3.1, R4.2, U$2.5 (ADJUST)
unnamed: C11.1, IC2.7 (PB6(XTAL1/TOSC1)), Q1.2
unnamed: C12.1, IC2.8 (PB7(XTAL2/TOSC2)), Q1.1
unnamed: U$4.A01(PRSNT1) (PRSNT1), U$4.A32(PRSNT2) (PRSNT2)
unnamed: U$6.EX_ANT, X1.1
PPS: IC2.1 (PD3(INT1)), TP5.TP, U2.P89 (IO_L04N_0/GCLK9), U$4.A26(PPS) (PPS), U$6.1PPS
PROG_B: JP4.5, R12.1, S1.3, S1.4, U2.P100 (PROG_B)
RESET_EEPROM: IC1.3 (!RESET), R13.1
SCK_EEPROM: IC1.2 (SCK), JP4.7, U2.P53 (IO_L12N_2/CCLK)
SLOWCLK/CLK: TP13.TP, U2.P85 (IO_L03P_0/GCLK6), U$4.A24(SLOWCLKCLK) (SLOWCLKCLK)
SLOWCLK/CS: TP14.TP, U2.P98 (IO_L06P_0/VREF_0), U$4.A25(SLOWCLK/CS) (SLOWCLK/CS)
SLOWCLK/MOSI: TP15.TP, U2.P99 (IO_L06N_0/PUDC_B), U$4.A23(SLOWTIMEMOSI) (SLOWCLKMOSI)
TCK: JP1.3, JP2.8, R11.2, U$4.A15(TCK) (TCK)
TDI: JP1.5, JP2.4, R10.2, U$4.A12(TDI) (TDI)
TDO: JP1.4, JP2.6, U2.P75 (TDO), U$4.A13(TDO) (TDO)
TIMING_CLK: QG1.5 (OUT), TP8.TP, U2.P84 (IO_L02N_0/GCLK5)
TIMING_RESET: IC2.24 (PC1(ADC1)), R19.2, U2.P93 (IO_L05P_0)
TMS: JP1.6, JP2.2, R9.2, U$4.A14(TMS) (TMS)
TRST: U$4.A16(TRST) (TRST)
UC_FPGA_SPI_CS: IC2.23 (PC0(ADC0)), R18.2, TP17.TP, U2.P90 (IO_0/GCLK11)
UC_MISO: IC2.16 (PB4(MISO)), JP3.9
UC_MOSI: IC2.15 (PB3(MOSI/OC2)), JP3.1, TP18.TP, U2.P97 (IP_0)
UC_RESET: IC2.29 (PC6(/RESET)), JP3.5
UC_SCK: IC2.17 (PB5(SCK)), JP3.7, TP16.TP, U2.P77 (IO_L01P_0/VREF_0)
USBVCC: U$6.USB-VCC, X2.1
VCC1.2: C6.1, C9.+, C18.1, C19.1, C20.1, C24.1, R8.2, TP4.TP, U2.P17 (VCCINT), U2.P38 (VCCINT), U2.P66 (VCCINT), U2.P81 (VCCINT), U$3.4 (VOUT), U$3.5 (ADJUST)
VCC2.5: C5.1, C8.+, C21.1, C22.1, C23.1, R3.2, R7.2, R12.2, TP3.TP, U2.P22 (VCCAUX), U2.P55 (VCCAUX), U2.P92 (VCCAUX), U$2.4 (VOUT), U$3.1 (ENABLE)
VCC3.3: C4.1, C7.+, C13.1, C14.1, C15.1, C16.1, IC1.6 (VCC), IC2.4 (VCC), IC2.6 (VCC), IC2.18 (AVCC), IC3.8 (VCC), JP1.1, JP2.10, JP3.2, JP4.2, QG1.8 (VCC), QG2.8 (VCC), R1.2, R6.2, R13.2, R14.2, R15.2, TP2.TP, U$1.4 (VOUT), U$6.VBACKUP, U$6.VCC
WP_EEPROM: IC1.5 (!WP), R14.1

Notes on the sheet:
Shorten two present pins!
Power
Timing_Clock
FPGA I/O Pins
FPGA_to_EEPROM
Microcontroller
JTAG
Friendship_Connector
FPGA_SPI_Clock
Testpoints

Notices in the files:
hardware/braeburn/braeburn1/braeburn.brd:
cc-by-nc-sa
hardware/friendship/friendship_v0/frienship_1.brd:
(CC-BY-NC-SA 3.0) 2012
